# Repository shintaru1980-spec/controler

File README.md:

# ProMicro_27Button

27-button matrix controller board for DTS-24N switches, using a separate Pro Micro module.

## Current reference configuration

- Pro Micro: Amazon B0DMNBJHT7, USB-C, ATmega32U4, 5 V / 16 MHz.
- Module provisional outline: 17.78 x 33.02 mm, using the common Pro Micro 24-pin THT geometry.
- Host board: 150 x 120 mm, 1.6 mm, two copper layers (preliminary layout).
- Button pitch: 19 mm horizontal and vertical.
- Button arrangement: 3 / 6 / 6 / 6 / 6, with the first row left-aligned.
- USB exit: USB-C connector faces right in the top view; the Pro Micro is rotated +90 degrees.
- Switch holes: 4 x 1.2 mm per DTS-24N, centers 12.5 mm horizontally and 5.0 mm vertically.
- Pro Micro header holes: 1.1 mm host drill, based on the official 1.016 mm module pad drill and intended for common square headers.

## Electrical mapping

Each switch is `ROW -> DTS-24N -> diode anode (A) -> diode cathode (K) -> COL`.

- ROW1..ROW5 = Pro Micro D2, D3, D4, D5, D6.
- COL1..COL6 = Pro Micro A2, A1, A0, D15, D14, D16.
- DTS-24N pads 1-2 are the row side; pads 3-4 are internally common and are the diode-anode side.
- D01..D27 are 1N4148WS SOD-323. Pad 2 is A and faces the switch; pad 1 is K and faces the column bus.

`wiring_map.csv` is the assembly/wiring reference for every button.

## JLCPCB assembly plan

The 27 diodes are SMD and are included in `BOM.csv` and `CPL.csv` for JLCPCB SMT assembly. The chosen provisional JLCPCB part is 1N4148WS SOD-323, C493187. Confirm current stock and the exact selected part at order time. DTS-24N and the Pro Micro module remain hand-soldered unless a separate THT assembly request is made.

## Important release gate

The linked Amazon product image shows USB-C and the listing specifies ATmega32U4, 5 V / 16 MHz, but the listing does not provide a mechanical drawing. This draft therefore assumes the common 24-pin Pro Micro THT pattern, 2.54 mm pitch, 17.78 x 33.02 mm body, and 1.1 mm host drills. Before ordering, measure one actual module: body width/length, both header-row centers, first-hole edge offsets, and USB-C connector position/overhang. Do not release Gerbers if those measurements differ. Some units may also omit USB-C CC pull-down resistors; verify USB-C-to-USB-C operation separately.

## Files

- `ProMicro_27Button.kicad_pcb`: routed two-layer PCB.
- `ProMicro_27Button.sch`: portable legacy KiCad schematic overview.
- `wiring_map.csv`: button-by-button net map.
- `BOM.csv`: parts and assembly responsibility.
- `CPL.csv`: diode placement file for SMT assembly.
- `JLCPCB_BOM.csv`: JLCPCB upload BOM containing only D01-D27.
- `JLCPCB_CPL.csv`: JLCPCB upload centroid file containing only D01-D27.
- `placement_preview.svg`: top-view placement preview.
- `generate_promicro_design.py`: reproducible generator.

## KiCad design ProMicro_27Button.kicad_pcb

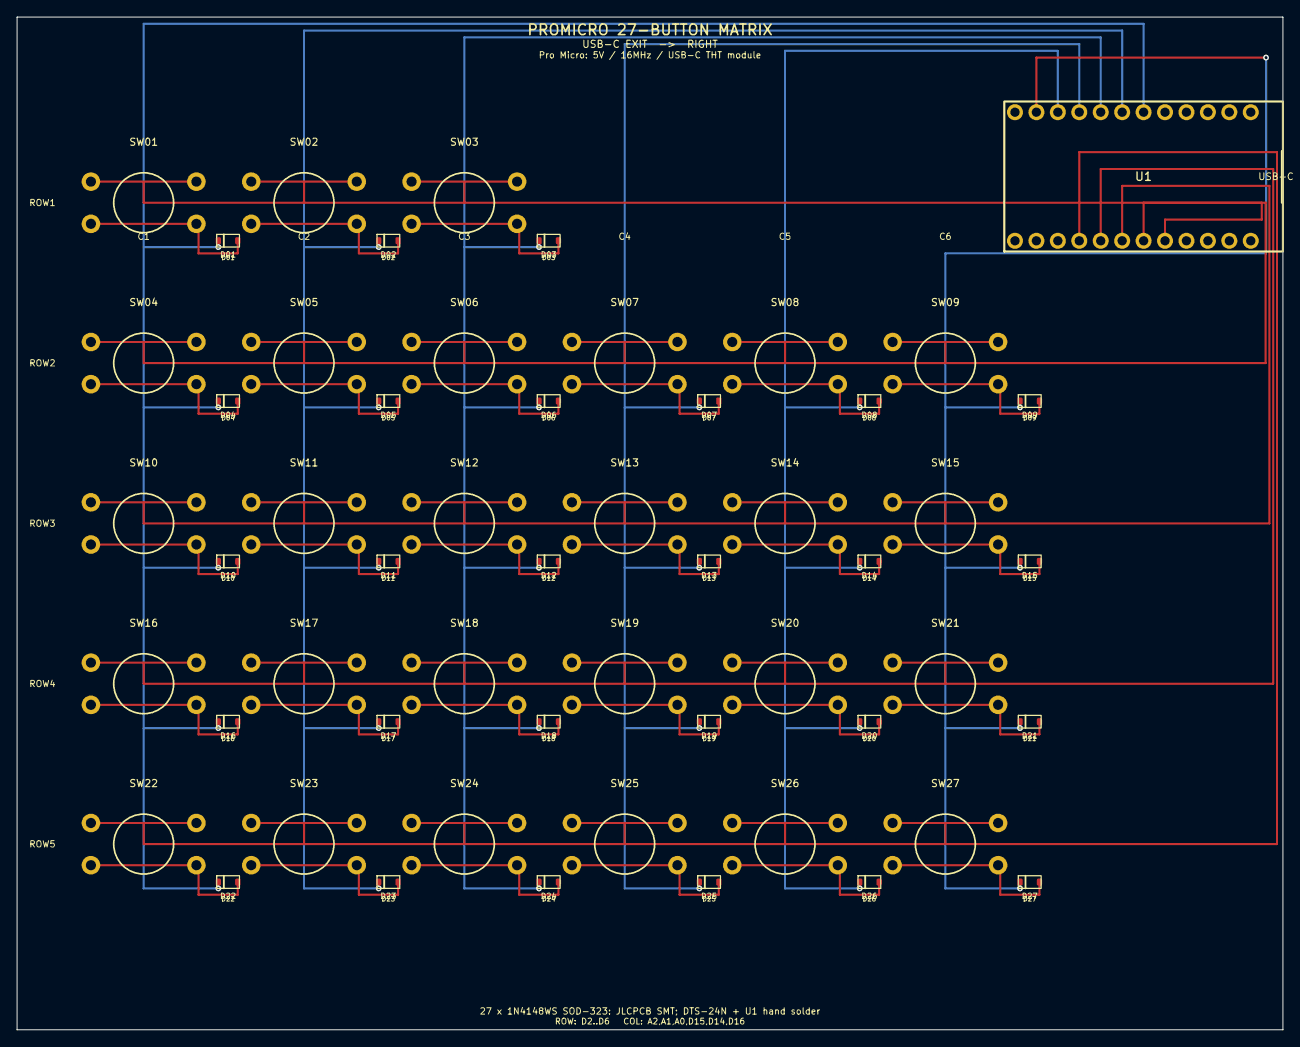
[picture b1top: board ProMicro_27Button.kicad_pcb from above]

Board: 2 copper layers, 150.0 x 120.0 mm, 55 parts (0 on the bottom side), 38 nets.

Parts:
D01, D02, D03, D04, D05, D06, D07, D08, D09, D10, D11, D12, D13, D14, D15, D16, D17, D18, D19, D20, D21, D22, D23, D24, D25, D26, D27: 1N4148WS; D_SOD-323_1N4148WS
SW01, SW02, SW03, SW04, SW05, SW06, SW07, SW08, SW09, SW10, SW11, SW12, SW13, SW14, SW15, SW16, SW17, SW18, SW19, SW20, SW21, SW22, SW23, SW24, SW25, SW26, SW27: DTS-24N
U1: Pro Micro 5V/16MHz USB-C THT; Pro_Micro_USB-C_5V16MHz_THT

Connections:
COL1: D01.1, D04.1, D10.1, D16.1, D22.1, U1.A2
COL2: D02.1, D05.1, D11.1, D17.1, D23.1, U1.A1
COL3: D03.1, D06.1, D12.1, D18.1, D24.1, U1.A0
COL4: D07.1, D13.1, D19.1, D25.1, U1.D15
COL5: D08.1, D14.1, D20.1, D26.1, U1.D14
COL6: D09.1, D15.1, D21.1, D27.1, U1.D16
D01_A: D01.2, SW01.3, SW01.4
D02_A: D02.2, SW02.3, SW02.4
D03_A: D03.2, SW03.3, SW03.4
D04_A: D04.2, SW04.3, SW04.4
D05_A: D05.2, SW05.3, SW05.4
D06_A: D06.2, SW06.3, SW06.4
D07_A: D07.2, SW07.3, SW07.4
D08_A: D08.2, SW08.3, SW08.4
D09_A: D09.2, SW09.3, SW09.4
D10_A: D10.2, SW10.3, SW10.4
D11_A: D11.2, SW11.3, SW11.4
D12_A: D12.2, SW12.3, SW12.4
D13_A: D13.2, SW13.3, SW13.4
D14_A: D14.2, SW14.3, SW14.4
D15_A: D15.2, SW15.3, SW15.4
D16_A: D16.2, SW16.3, SW16.4
D17_A: D17.2, SW17.3, SW17.4
D18_A: D18.2, SW18.3, SW18.4
D19_A: D19.2, SW19.3, SW19.4
D20_A: D20.2, SW20.3, SW20.4
D21_A: D21.2, SW21.3, SW21.4
D22_A: D22.2, SW22.3, SW22.4
D23_A: D23.2, SW23.3, SW23.4
D24_A: D24.2, SW24.3, SW24.4
D25_A: D25.2, SW25.3, SW25.4
D26_A: D26.2, SW26.3, SW26.4
D27_A: D27.2, SW27.3, SW27.4
ROW1: SW01.1, SW01.2, SW02.1, SW02.2, SW03.1, SW03.2, U1.D2
ROW2: SW04.1, SW04.2, SW05.1, SW05.2, SW06.1, SW06.2, SW07.1, SW07.2, SW08.1, SW08.2, SW09.1, SW09.2, U1.D3
ROW3: SW10.1, SW10.2, SW11.1, SW11.2, SW12.1, SW12.2, SW13.1, SW13.2, SW14.1, SW14.2, SW15.1, SW15.2, U1.D4
ROW4: SW16.1, SW16.2, SW17.1, SW17.2, SW18.1, SW18.2, SW19.1, SW19.2, SW20.1, SW20.2, SW21.1, SW21.2, U1.D5
ROW5: SW22.1, SW22.2, SW23.1, SW23.2, SW24.1, SW24.2, SW25.1, SW25.2, SW26.1, SW26.2, SW27.1, SW27.2, U1.D6

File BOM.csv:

References,Quantity,Value,Package,Assembly,JLCPCB/LCSC part,Notes
D01-D27,27,1N4148WS,SOD-323,JLCPCB SMT,C493187,JLCPCB listing; verify stock at order time
SW01-SW27,27,DTS-24N,THT 4-hole,Hand solder,,DTS-2 datasheet footprint; 1.2 mm holes
U1,1,Pro Micro USB-C 5V/16MHz,24-pin THT module,Hand solder / socket,Amazon B0DMNBJHT7,Assumed classic Pro Micro 2.54 mm hole pattern; verify actual clone

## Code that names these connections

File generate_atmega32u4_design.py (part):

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    add_zone(d, "GND", "F.Cu")
    add_zone(d, "GND", "B.Cu")
    add_zone_rect(d, "+5V", "B.Cu", 127.0, 0.5, 149.0, 15.5, 1)
    for i, name in enumerate(["PF0/ROW1", "PF1/ROW2", "PF4/ROW3",
                              "PF5/ROW4", "PF6/ROW5"]):
        d.text(name, 104, 5.0 + i * 1.6, 0.65)
    for i, name in enumerate(["PB7/COL1", "PD0/COL2", "PD1/COL3",
                              "PD2/COL4", "PD3/COL5", "PD5/COL6"]):
        d.text(name, 144.0, 104.0 + i * 1.5, 0.6)
    for r, y in enumerate(BUTTON_YS):
        d.text(f"ROW{r + 1}", 4.0, y - 2.5, 0.65)
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        "Text Notes 800 1350 0    80   ~ 16",
        "ICSP J2: 1=MISO 2=+5V 3=SCK 4=MOSI 5=RESET 6=GND",
        "Text Notes 800 1550 0    80   ~ 16",
        "Matrix rows: PF0/PF1/PF4/PF5/PF6 = ROW1..ROW5",
        "Text Notes 800 1750 0    80   ~ 16",
        "Matrix columns: PB7/PD0/PD1/PD2/PD3/PD5 = COL1..COL6",
        "Text Notes 800 2050 0    90   ~ 18",
        "DTS-24N internal contact: pins 1-2 are one side; pins 3-4 are the other.",
        "Text Notes 800 2250 0    90   ~ 18",
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
## MCUの接続

- ROW1..ROW5 = PF0, PF1, PF4, PF5, PF6（U1 pin 36,37,38,39,40）
- COL1..COL6 = PB7, PD0, PD1, PD2, PD3, PD5（U1 pin 12,18,19,20,21,22）
- USB D- / D+ = U1 pin 3 / 4
- RESET = U1 pin 13、HWB = U1 pin 33
- USB-C CC1/CC2には各5.1 kΩのGNDプルダウン
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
